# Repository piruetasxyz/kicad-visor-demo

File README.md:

# kicad-visor-demo

## About

A working example of [kicad-visor](https://github.com/piruetasxyz/kicad-visor) by [piruetas](https://piruetas.xyz): on every push to `main`, a GitHub Actions workflow exports every KiCad project in this repository (schematics, board layers, 3D renders and seamlessly looping turntable videos) and publishes them as a website: <https://piruetas.xyz/kicad-visor-demo/>. Each board keeps its own license (see below).

## Acerca de

Ejemplo de [kicad-visor](https://github.com/piruetasxyz/kicad-visor), de [piruetas](https://piruetas.xyz). Cada vez que se hace push a `main`, un workflow de GitHub Actions exporta todos los proyectos KiCad de este repositorio y los publica como sitio web en <https://piruetas.xyz/kicad-visor-demo/>.

Por cada placa, el sitio muestra:

- el esquemático, en svg, png, jpg y pdf.
- la placa en 2D: frente, reverso, cobre y cada capa por separado.
- renders 3D: arriba, abajo, isométricas y perspectiva.
- videos turntable que se repiten sin cortes, en formato horizontal, vertical y cuadrado, sobre distintos colores de fondo.

## Placas

| placa | qué es | repositorio |
|-------|--------|-------------|
| [chufe](./chufe) | fuente de alimentación eurorack: entrada de 12 V DC, salidas ±12V y +5V | [piruetasxyz/chufe](https://github.com/piruetasxyz/chufe) |
| [chufebu](./chufebu) | bus de alimentación eurorack: 5 headers de 16 pines, cada uno con su conector Molex KK-396 | [piruetasxyz/chufebu](https://github.com/piruetasxyz/chufebu) |

Las placas son copias de sus repositorios, con la misma estructura de carpetas (`hardware/` y, en chufe, `terceros/`), para que las rutas de los modelos 3D y de las bibliotecas funcionen sin cambios. Para actualizar una placa, hay que copiar de nuevo su carpeta `hardware/` desde su repositorio.

## Cómo funciona

El workflow está en [.github/workflows/kicad-visor.yml](.github/workflows/kicad-visor.yml). Corre dentro de la imagen oficial `kicad/kicad:10.0-full` (KiCad 10 con sus modelos 3D), instala kicad-visor y ejecuta:

```bash
kicad-visor export . --output _site --only schematic,pcb,render,turntable
```

El resultado se publica directamente en GitHub Pages, sin hacer commit de los renders. Los frames de los videos quedan en caché entre ejecuciones: la primera vez se demora decenas de minutos por placa, y después solamente se vuelven a renderizar las placas que cambian.

Para usarlo con tus propias placas, sigue las instrucciones de [kicad-visor](https://github.com/piruetasxyz/kicad-visor#publishing-to-github-pages).

## Licencias

Cada placa conserva su propia licencia, en su carpeta: hardware bajo CERN-OHL-P-2.0 y documentación bajo CC-BY-SA-4.0. Ver [chufe/LICENSE.md](./chufe/LICENSE.md) y [chufebu/LICENSE.md](./chufebu/LICENSE.md). Los componentes de terceros de chufe, en `chufe/terceros/`, no son obra de piruetas: ver [chufe/LICENSES/LicenseRef-easyeda.txt](./chufe/LICENSES/LicenseRef-easyeda.txt).

## Acerca de piruetas

[piruetas](https://piruetas.xyz) es un estudio de arte chileno fundado en 2022 por [montoyamoraga](https://montoyamoraga.io), con base en Santiago de Chile.

- web: [piruetas.xyz](https://piruetas.xyz)
- github: [github.com/piruetasxyz](https://github.com/piruetasxyz)
- instagram: [@piruetas.xyz](https://instagram.com/piruetas.xyz)

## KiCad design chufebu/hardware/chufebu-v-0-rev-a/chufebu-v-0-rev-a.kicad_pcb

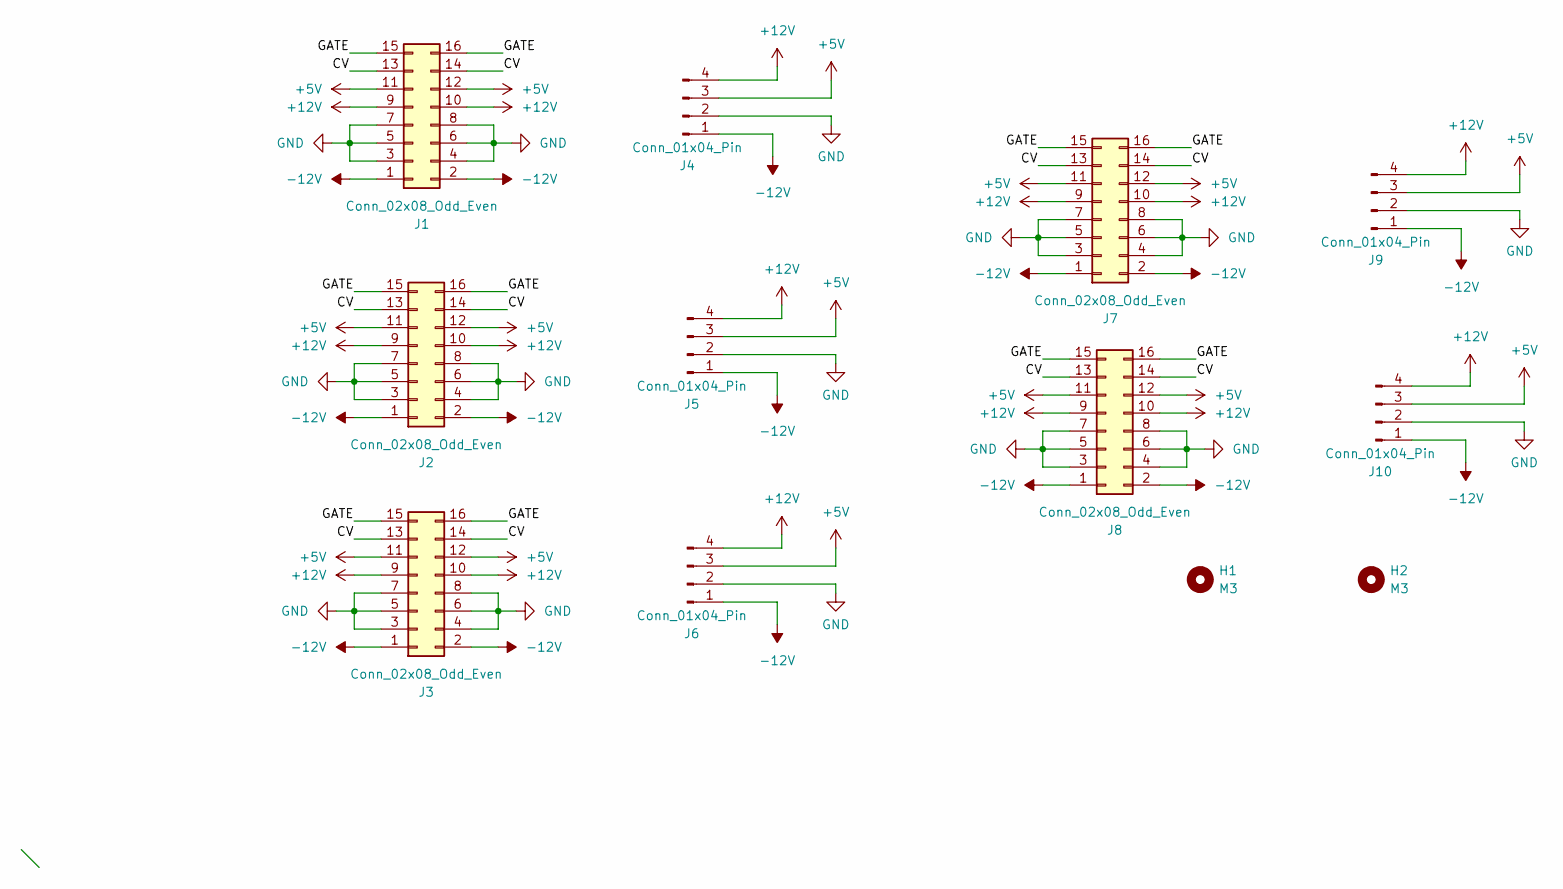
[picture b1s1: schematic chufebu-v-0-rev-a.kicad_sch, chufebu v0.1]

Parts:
H1, H2: M3; MountingHole_3.2mm_M3
J1, J2, J3, J7, J8: Conn_02x08_Odd_Even; IDC-Header_2x08_P2.54mm_Vertical
J4, J5, J6, J9, J10: Conn_01x04_Pin; Molex_KK-396_5273-04A_1x04_P3.96mm_Vertical

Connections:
+5V: J1.11, J1.12, J2.11, J2.12, J3.11, J3.12, J4.3, J5.3, J6.3, J7.11, J7.12, J8.11, J8.12, J9.3, J10.3
+12V: J1.9, J1.10, J2.9, J2.10, J3.9, J3.10, J4.4, J5.4, J6.4, J7.9, J7.10, J8.9, J8.10, J9.4, J10.4
-12V: J1.1, J1.2, J2.1, J2.2, J3.1, J3.2, J4.1, J5.1, J6.1, J7.1, J7.2, J8.1, J8.2, J9.1, J10.1
/CV: J1.13, J1.14, J2.13, J2.14, J3.13, J3.14, J7.13, J7.14, J8.13, J8.14
/GATE: J1.15, J1.16, J2.15, J2.16, J3.15, J3.16, J7.15, J7.16, J8.15, J8.16
GND: J1.3, J1.4, J1.5, J1.6, J1.7, J1.8, J2.3, J2.4, J2.5, J2.6, J2.7, J2.8, J3.3, J3.4, J3.5, J3.6, J3.7, J3.8, J4.2, J5.2, J6.2, J7.3, J7.4, J7.5, J7.6, J7.7, J7.8, J8.3, J8.4, J8.5, J8.6, J8.7, J8.8, J9.2, J10.2

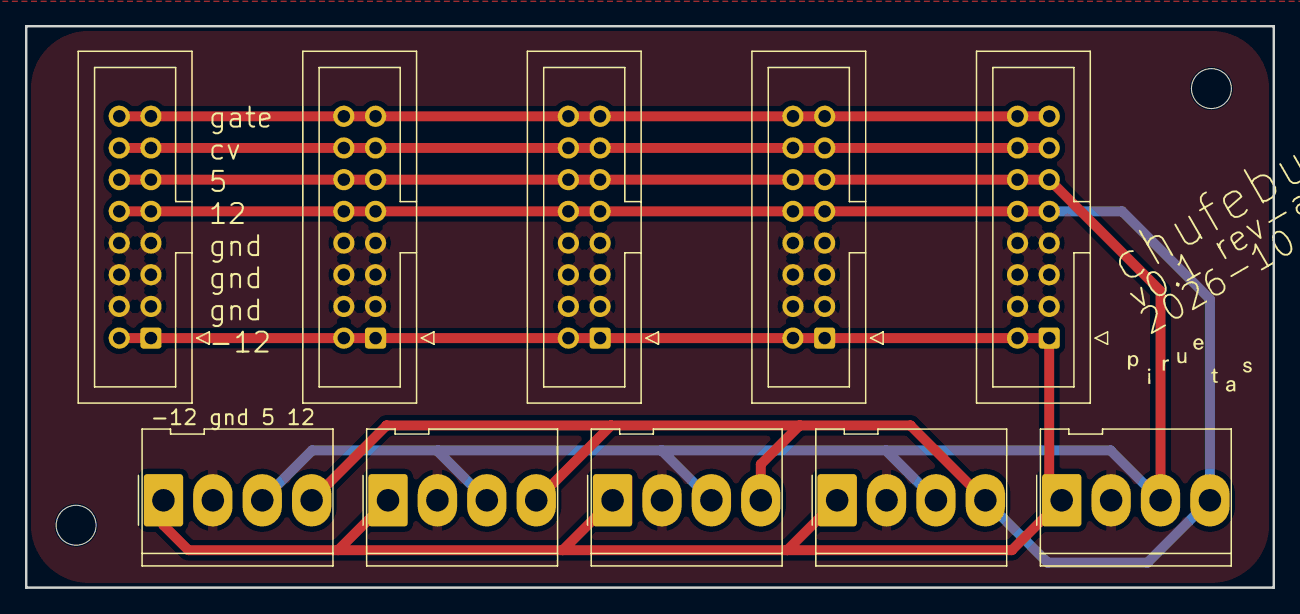
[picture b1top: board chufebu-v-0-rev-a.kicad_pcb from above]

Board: 2 copper layers, 100.0 x 45.0 mm, 12 parts (0 on the bottom side), 6 nets.

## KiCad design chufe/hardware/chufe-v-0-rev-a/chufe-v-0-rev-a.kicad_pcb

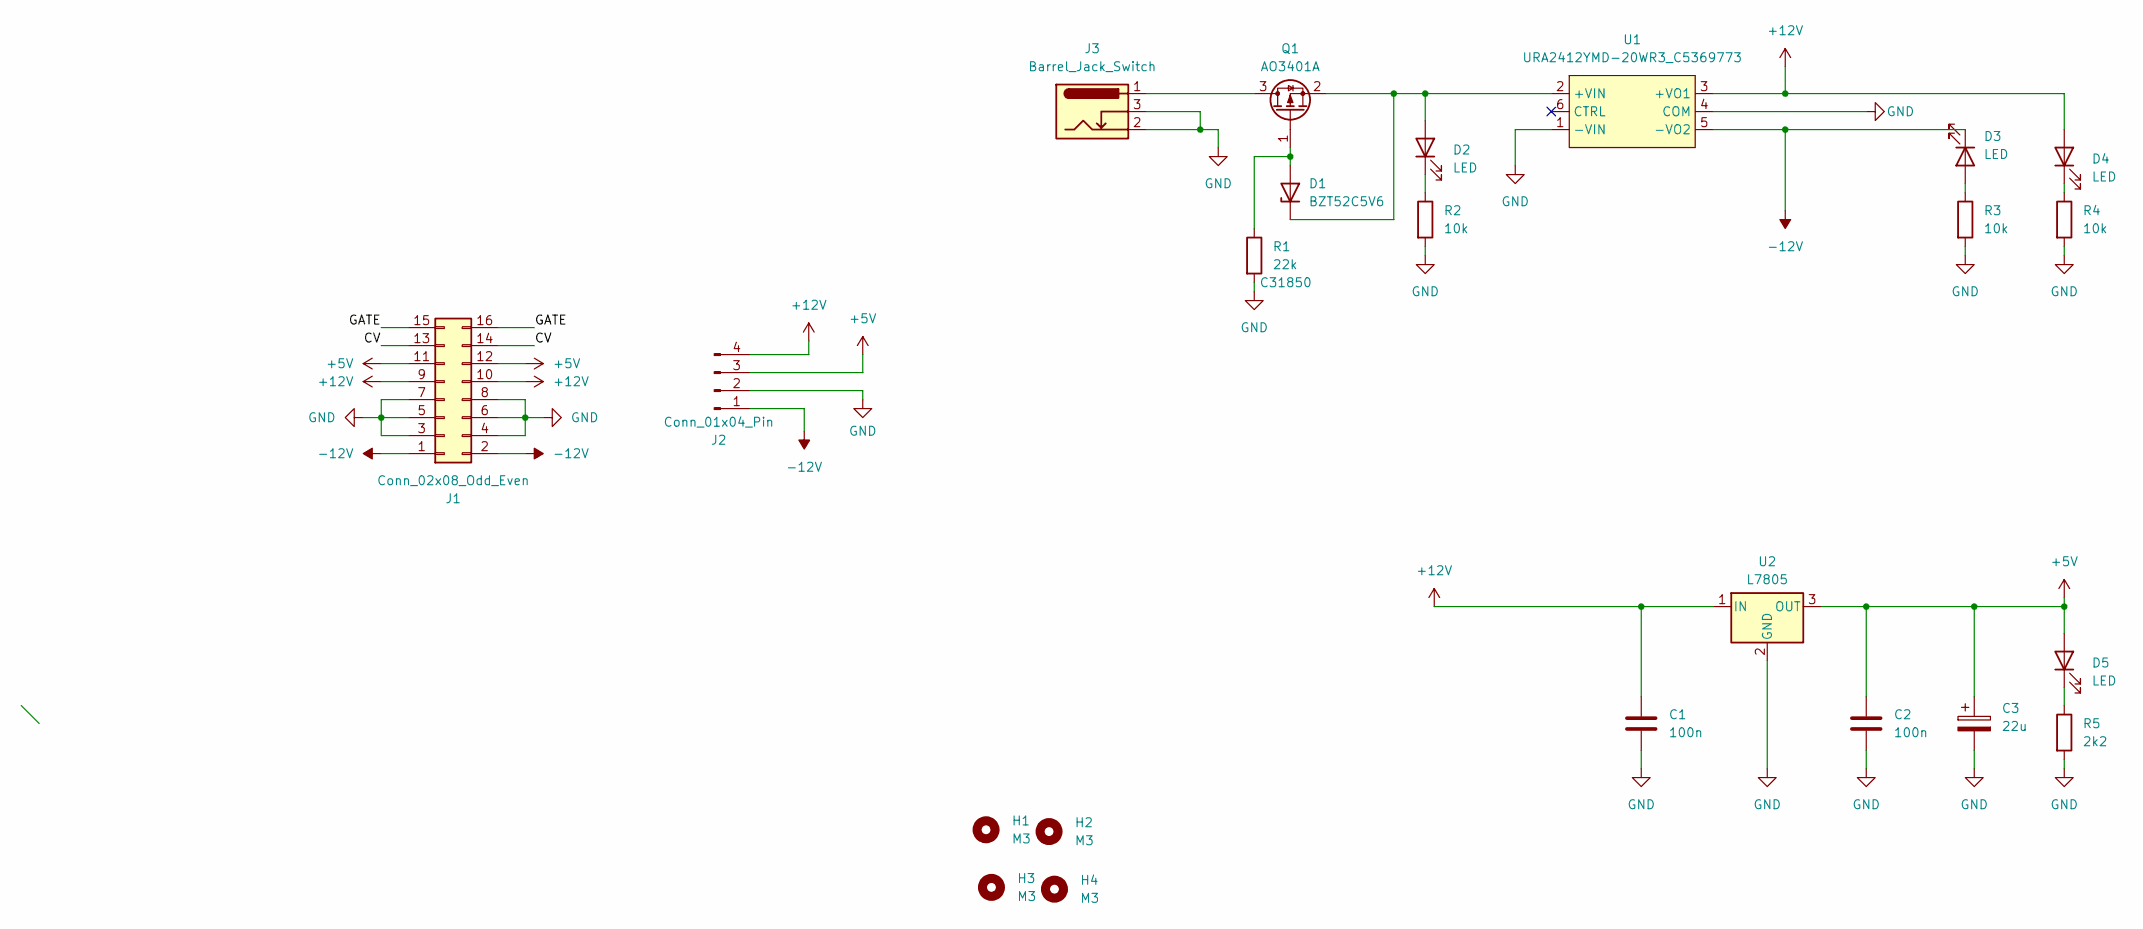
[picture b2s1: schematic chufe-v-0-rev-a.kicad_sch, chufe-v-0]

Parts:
C1, C2: 100n; C_0805_2012Metric; LCSC C49678
C3: 22u; CP_Elec_4x5.4; LCSC C72502
D1: BZT52C5V6; D_SOD-123; LCSC C19077402
D2, D3, D4, D5: LED; LED_D3.0mm
H1, H2, H3, H4: M3; MountingHole_3.2mm_M3
J1: Conn_02x08_Odd_Even; IDC-Header_2x08_P2.54mm_Vertical
J2: Conn_01x04_Pin; Molex_KK-396_5273-04A_1x04_P3.96mm_Vertical
J3: Barrel_Jack_Switch; BarrelJack_Horizontal
Q1: AO3401A; SOT-23; LCSC C15127
R1: 22k; R_0805_2012Metric; LCSC C31850
R2, R3, R4: 10k; R_0805_2012Metric; LCSC C17414
R5: 2k2; R_0805_2012Metric; LCSC C17520
U1: URA2412YMD-20WR3_C5369773; PWRM-TH_YLPTEC_VRBXXXXYMD-20WR3; MPN URA2412YMD-20WR3; LCSC Part C5369773
U2: L7805; TO-252-2; LCSC C19626525

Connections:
+5V: C2.1, C3.1, D5.2 (A), J1.11, J1.12, J2.3, U2.3 (OUT)
+12V: C1.1, D4.2 (A), J1.9, J1.10, J2.4, U1.3 (+VO1), U2.1 (IN)
-12V: D3.1 (K), J1.1, J1.2, J2.1, U1.5 (-VO2)
/CV: J1.13, J1.14
/GATE: J1.15, J1.16
GND: C1.2, C2.2, C3.2, J1.3, J1.4, J1.5, J1.6, J1.7, J1.8, J2.2, J3.2, J3.3, R1.2, R2.2, R3.2, R4.2, R5.2, U1.1 (-VIN), U1.4 (COM), U2.2 (GND)
unnamed: D1.2 (A), Q1.1 (G), R1.1
unnamed: D1.1 (K), D2.2 (A), Q1.2 (S), U1.2 (+VIN)
unnamed: D2.1 (K), R2.1
unnamed: D3.2 (A), R3.1
unnamed: D4.1 (K), R4.1
unnamed: D5.1 (K), R5.1
unnamed: J3.1, Q1.3 (D)

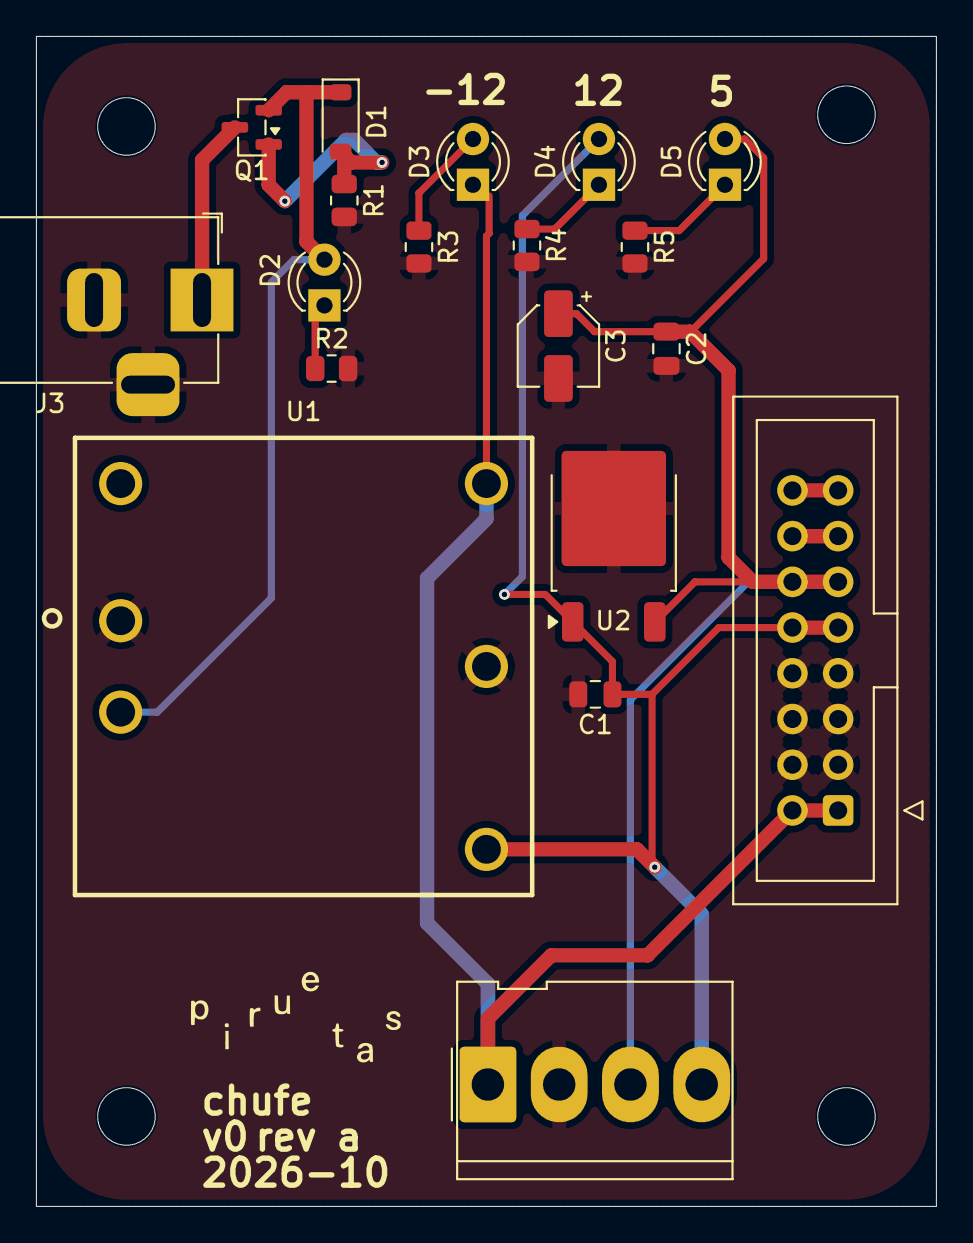
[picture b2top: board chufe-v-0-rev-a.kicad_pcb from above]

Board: 2 copper layers, 50.0 x 65.0 mm, 23 parts (0 on the bottom side), 13 nets.
